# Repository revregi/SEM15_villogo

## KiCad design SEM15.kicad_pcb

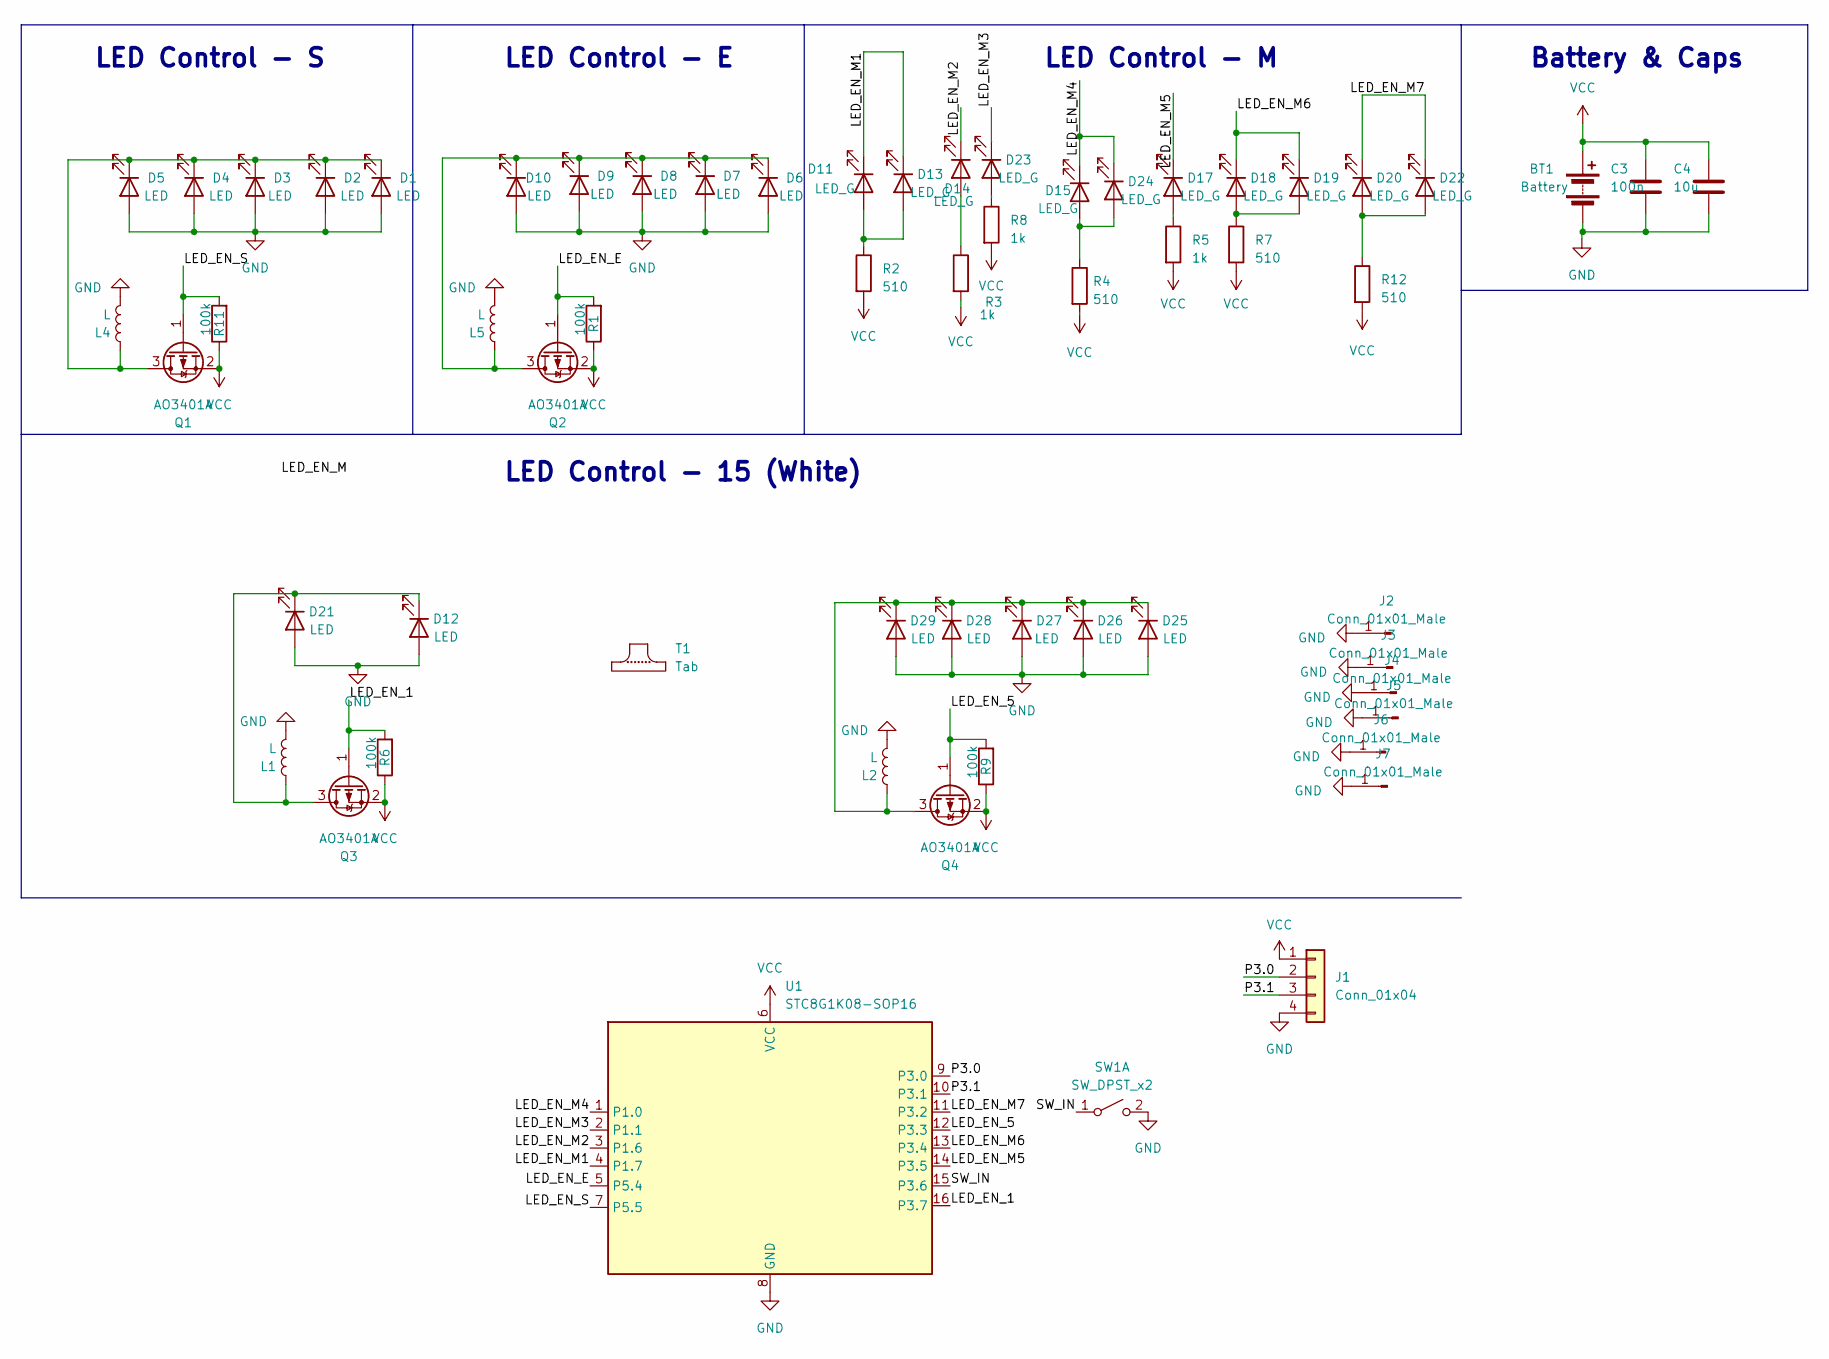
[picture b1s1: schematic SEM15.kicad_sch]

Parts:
BT1: Battery; CR2032_Holder
C3: 100n; C_0805_2012Metric
C4: 10u; C_0805_2012Metric
D1, D2, D3, D4, D5, D6, D7, D8, D9, D10, D12, D21, D25, D26, D27, D28, D29: LED; LED_0805_2012Metric
D11, D13, D14, D15, D17, D18, D19, D20, D22, D23, D24: LED_G; LED_0805_2012Metric
J1: Conn_01x04; PinHeader_1x04_P1.27mm_Vertical
J2, J3, J4, J5, J6, J7: Conn_01x01_Male; PinHeader_1x01_P2.54mm_Vertical
L1, L2, L4, L5: L; L_1008_2520Metric
Q1, Q2, Q3, Q4: AO3401A; SOT-23
R1, R6, R9, R11: 100k; R_0603_1608Metric
R2, R4, R7, R12: 510; R_0603_1608Metric
R3, R5, R8: 1k; R_0603_1608Metric
SW1: SW_DPST_x2; SW_Push_TS-1187A
T1: Tab
U1: STC8G1K08-SOP16; STC_SOP-16_3.9x9.9mm_P1.27mm

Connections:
/LED_EN_1: Q3.1 (G), R6.2, U1.16 (P3.7)
/LED_EN_5: Q4.1 (G), R9.2, U1.12 (P3.3)
/LED_EN_E: Q2.1 (G), R1.2, U1.5 (P5.4)
/LED_EN_M1: D11.1 (K), D13.1 (K), U1.4 (P1.7)
/LED_EN_M2: D14.1 (K), U1.3 (P1.6)
/LED_EN_M3: D23.1 (K), U1.2 (P1.1)
/LED_EN_M4: D15.1 (K), D24.1 (K), U1.1 (P1.0)
/LED_EN_M5: D17.1 (K), U1.14 (P3.5)
/LED_EN_M6: D18.1 (K), D19.1 (K), U1.13 (P3.4)
/LED_EN_M7: D20.1 (K), D22.1 (K), U1.11 (P3.2)
/LED_EN_S: Q1.1 (G), R11.2, U1.7 (P5.5)
/P3.0: J1.2, U1.9 (P3.0)
/P3.1: J1.3, U1.10 (P3.1)
/SW_IN: SW1.1 (A), U1.15 (P3.6)
GND: BT1.2 (-), C3.2, C4.2, D1.2 (A), D2.2 (A), D3.2 (A), D4.2 (A), D5.2 (A), D6.2 (A), D7.2 (A), D8.2 (A), D9.2 (A), D10.2 (A), D12.2 (A), D21.2 (A), D25.2 (A), D26.2 (A), D27.2 (A), D28.2 (A), D29.2 (A), J1.4, J2.1, J3.1, J4.1, J5.1, J6.1, J7.1, L1.2, L2.2, L4.2, L5.2, SW1.2 (B), U1.8 (GND); also elsewhere on the board
unnamed: D1.1 (K), D2.1 (K), D3.1 (K), D4.1 (K), D5.1 (K), L4.1, Q1.3 (D)
unnamed: D6.1 (K), D7.1 (K), D8.1 (K), D9.1 (K), D10.1 (K), L5.1, Q2.3 (D)
unnamed: D11.2 (A), D13.2 (A), R2.1
unnamed: D12.1 (K), D21.1 (K), L1.1, Q3.3 (D)
unnamed: D14.2 (A), R3.1
unnamed: D15.2 (A), D24.2 (A), R4.1
unnamed: D17.2 (A), R5.1
unnamed: D18.2 (A), D19.2 (A), R7.1
unnamed: D20.2 (A), D22.2 (A), R12.1
unnamed: D23.2 (A), R8.1
unnamed: D25.1 (K), D26.1 (K), D27.1 (K), D28.1 (K), D29.1 (K), L2.1, Q4.3 (D)
VCC: BT1.1 (+), C3.1, C4.1, J1.1, Q1.2 (S), Q2.2 (S), Q3.2 (S), Q4.2 (S), R1.1, R2.2, R3.2, R4.2, R5.2, R6.1, R7.2, R8.2, R9.1, R11.1, R12.2, U1.6 (VCC)

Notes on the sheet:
LED Control - S
LED Control - E
LED Control - M
Battery & Caps
LED Control - 15 (White)

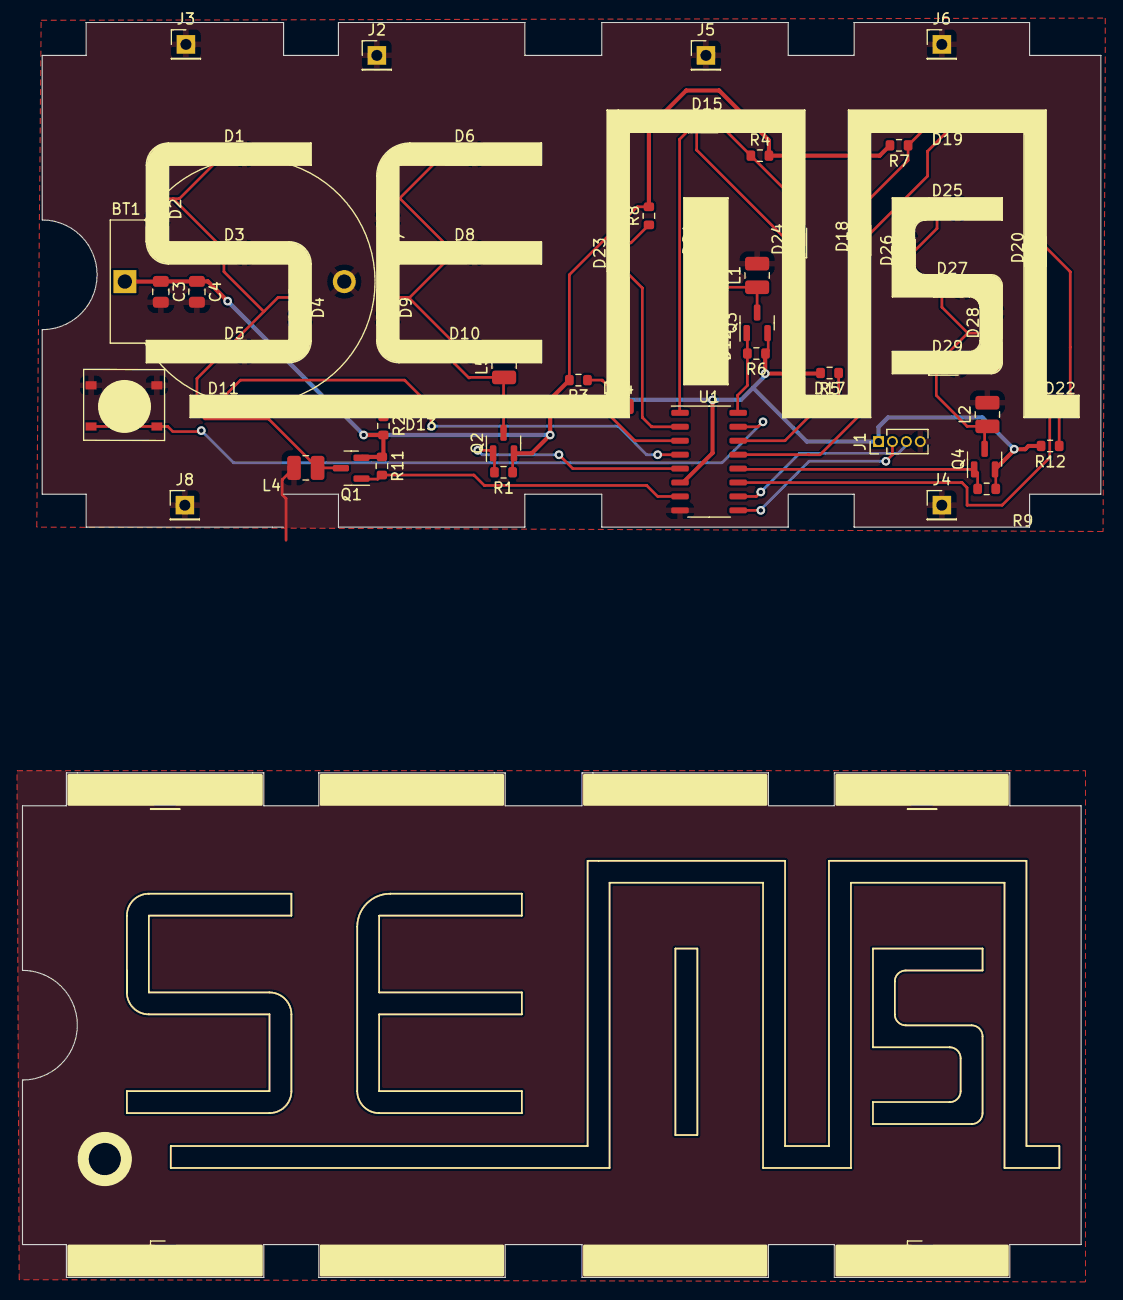
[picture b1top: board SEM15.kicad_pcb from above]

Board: 2 copper layers, 98.3 x 114.4 mm, 79 parts (0 on the bottom side), 27 nets.

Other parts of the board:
J2#2, J5#2, J8, J9: Conn_01x01_Male; PinHeader_1x01_P2.54mm_Vertical
T1#2, T1#3, T1#4, T1#5, T1#6, T1#7, T1#8, T1#9, T1#10, T1#11, T1#12, T1#13, T1#14, T1#15, T1#16: Tab

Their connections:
GND: J5#2.1, J8.1; also elsewhere on the board

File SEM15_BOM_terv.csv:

Comment,Designator,Footprint,JLCPCB Part #（optional）
100n,C3,0805,C49678
10u,C4,0805,C15850
LED WHITE,"D1,D2,D3,D4,D5,D6,D7,D8,D9,D10,D12,D17,D18,D19,D21,D25,D26,D27,D28,D29",0805,C34499
LED GREEN,"D11,D13,D14,D23,D15,D24,D17,D18,D19,D20,D22",0805,C2297
1mH,"L1,L2,L4,L5",1008,C223217
AO3401A,"Q1,Q2,Q3,Q4",SOT-23,C347476
100k,"R1,R6,R9,R11",0603,C25803
510,"R2,R4,R7,R12",0603,C73811
1k,"R3,R5,R8",0603,C21190
SW,SW1,SMD,??
STC8G1K08-SOP16,U1,SOP-16,C2901876

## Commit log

2023-10-22 rgb es feher led meghajtasa, mikrovezerlo, pcb-n alkatreszrendezgets
2023-10-23 sch kesz
2023-10-24 pcb nagyreszt
2023-10-25 Rezkitoltes
2023-10-25 rogzitok
2023-10-26 Panelizalas, BOM elkezdve.
2023-10-26 BOM terv
2023-10-26 uj gomb, kivagas
2023-10-26 top add silkscreen and fill other side
2023-10-26 gerberek, bom
2023-10-27 sent to jlc
2023-11-03 Added firmware.
2023-11-03 Fixed wake-up.
2023-11-19 Ported battery charge display.
2023-11-21 Animations by Ricsi
2023-11-21 Small tweak.
